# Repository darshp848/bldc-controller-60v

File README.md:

# bldc-controller-60v

A 48 V nominal / 60 V max BLDC motor controller that fits wherever a MAB Robotics MD80 v3.0
fits: same outline, mounting holes, Micro-Fit and AUX connectors, phase-wire holes and
encoder position, with the MD80's 20 A continuous / 80 A peak phase current.

## Status

| Item | State |
|---|---|
| Schematic (KiCad 10, 6 sheets, 137 symbols) | done, ERC 0 errors 0 warnings |
| PCB outline, holes, connectors vs MAB STEP | done, 36 holes match to 0.000 mm (`mech/fit_check.txt`) |
| PCB rev B (144 footprints, 6 layers) | routed; DRC: 0 unconnected, 1 error (MD80-inherent AUX1/screw overlap); two-shunt power stage, 5.0SMDJ60A TVS |
| Simulation | loop inductance, double pulse, bus surge, current loop: docs/simulation.md |
| Firmware | not started; pin map and bring-up values in docs/firmware.md |
| Bench validation | none; loss figures are estimates |

## Layout

```
hardware/            KiCad 10 project (open better-md80.kicad_pro)
  lib/               project symbol (DRV8353S) and MD80 footprints
  better-md80.kicad_dru   60 V clearance rules
docs/
  architecture.md    spec, what limits the MD80 to 48 V, part selection, power tree
  mechanical.md      MD80 fit data and what to verify before first power-up
  thermal_layout.md  loss budget, stack-up, layout rules
  firmware.md        pin map, clocks, DRV8353 settings, protection thresholds
  simulation.md      FastHenry / LTspice / MATLAB results and the changes they call for
  bom.csv            grouped BOM with MPNs
  schematic.pdf      all sheets
mech/                geometry extracted from MAB's MD80_V3.0_simplified.step
sim/                 simulation scripts (outputs in sim/out)
tools/               generators (design.py is the source of truth for the schematic)
```

## Regenerating

```bash
bash tools/build.sh
```

This rebuilds footprints, schematic, netlist, ERC/DRC reports, BOM, the schematic PDF and
the 3D renders. It leaves the routed PCB alone unless you run it with `REGEN_PCB=1`, which
regenerates the placement and throws the routing away (see tools/route.md to redo it).
Schematic changes reach the board through KiCad's Update PCB from Schematic as usual.

`tools/analyze_step.py` needs Python with CadQuery; everything else uses KiCad 10's
`kicad-cli` and bundled Python.

The KiCad files keep their original `better-md80` working name.

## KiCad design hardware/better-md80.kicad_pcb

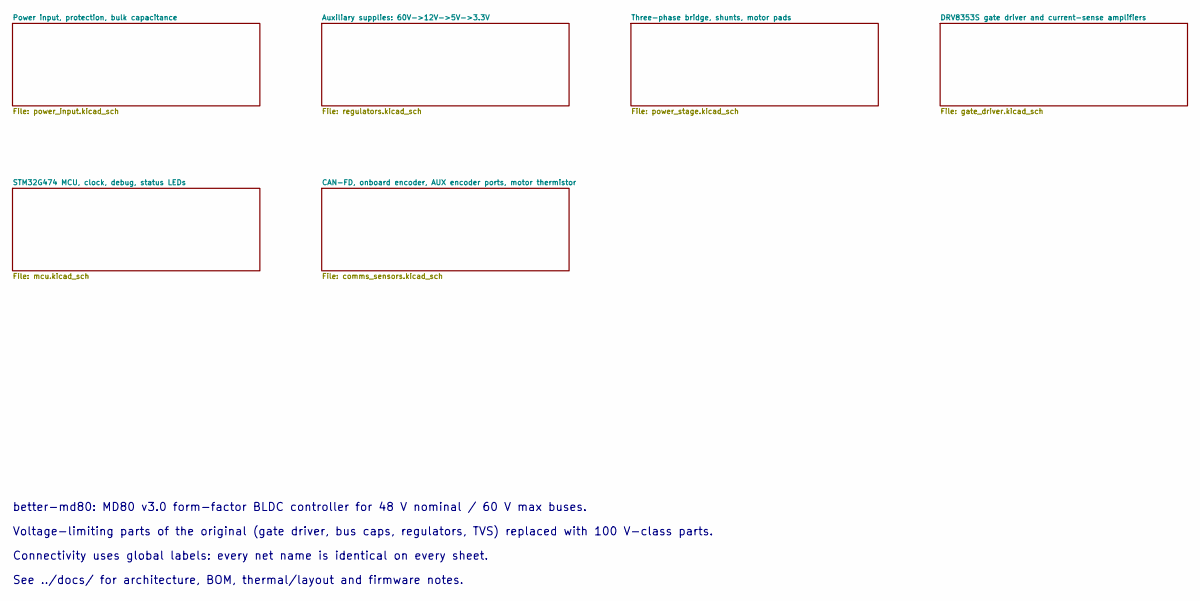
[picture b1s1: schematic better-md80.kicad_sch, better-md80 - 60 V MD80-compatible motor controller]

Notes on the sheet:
better-md80: MD80 v3.0 form-factor BLDC controller for 48 V nominal / 60 V max buses.
Connectivity uses global labels: every net name is identical on every sheet.
Voltage-limiting parts of the original (gate driver, bus caps, regulators, TVS) replaced with 100 V-class parts.
See ../docs/ for architecture, BOM, thermal/layout and firmware notes.

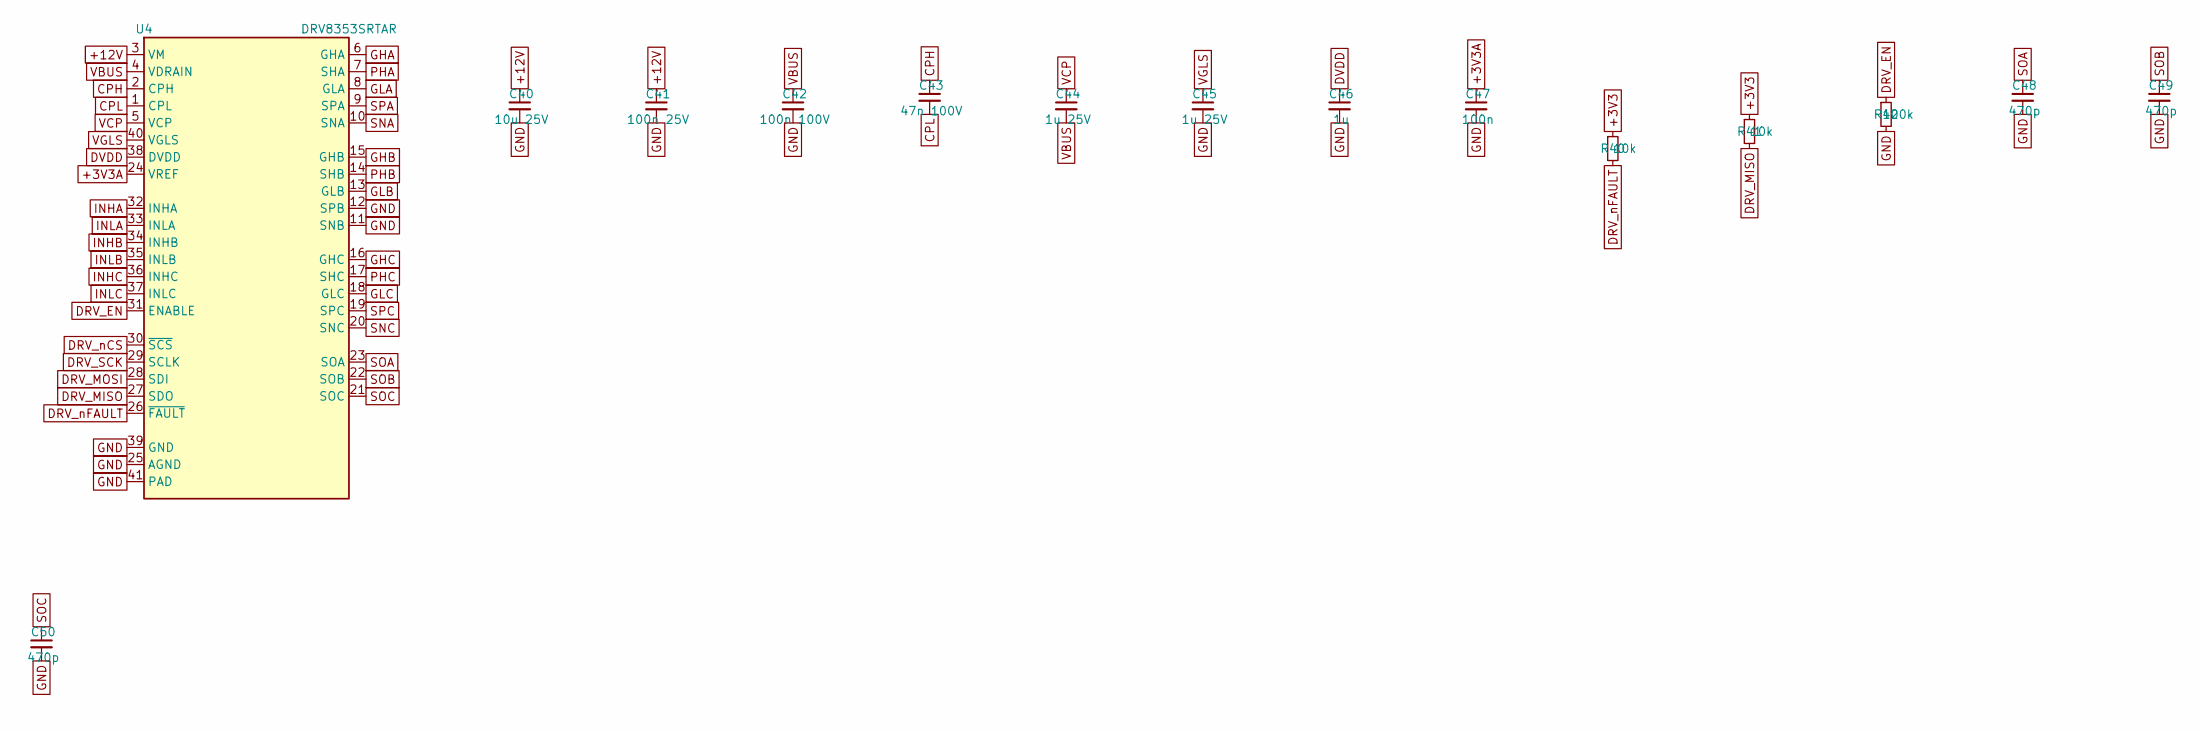
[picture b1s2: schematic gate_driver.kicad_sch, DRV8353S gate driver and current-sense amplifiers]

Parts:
C40: 10u 25V; C_0805_2012Metric
C41: 100n 25V; C_0402_1005Metric
C42: 100n 100V; C_0603_1608Metric; MPN Murata GRM188R72A104KA35D
C43: 47n 100V; C_0603_1608Metric; MPN Murata GRM188R72A473KA01D (verify)
C44, C45: 1u 25V; C_0603_1608Metric
C46: 1u; C_0402_1005Metric
C47: 100n; C_0402_1005Metric
C48, C49, C50: 470p; C_0402_1005Metric
R40, R41: 10k; R_0402_1005Metric
R42: 100k; R_0402_1005Metric
U4: DRV8353SRTAR; Texas_RHA0040B_VQFN-40-1EP_6x6mm_P0.5mm_EP4.15x4.15mm; MPN TI DRV8353SRTAR

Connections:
+3V3: R40.1, R41.1; also elsewhere on the board
+3V3A: C47.1, U4.24 (VREF); also elsewhere on the board
+12V: C40.1, C41.1, U4.3 (VM); also elsewhere on the board
CPH: C43.1, U4.2 (CPH)
CPL: C43.2, U4.1 (CPL)
DRV_EN: R42.1, U4.31 (ENABLE); also elsewhere on the board
DRV_MISO: R41.2, U4.27 (SDO); also elsewhere on the board
DRV_MOSI: U4.28 (SDI); also elsewhere on the board
DRV_SCK: U4.29 (SCLK); also elsewhere on the board
DRV_nCS: U4.30 (~SCS); also elsewhere on the board
DRV_nFAULT: R40.2, U4.26 (~FAULT); also elsewhere on the board
DVDD: C46.1, U4.38 (DVDD)
GHA: U4.6 (GHA); also elsewhere on the board
GHB: U4.15 (GHB); also elsewhere on the board
GHC: U4.16 (GHC); also elsewhere on the board
GLA: U4.8 (GLA); also elsewhere on the board
GLB: U4.13 (GLB); also elsewhere on the board
GLC: U4.18 (GLC); also elsewhere on the board
GND: C40.2, C41.2, C42.2, C45.2, C46.2, C47.2, C48.2, C49.2, C50.2, R42.2, U4.11 (SNB), U4.12 (SPB), U4.25 (AGND), U4.39 (GND), U4.41 (PAD); also elsewhere on the board
INHA: U4.32 (INHA); also elsewhere on the board
INHB: U4.34 (INHB); also elsewhere on the board
INHC: U4.36 (INHC); also elsewhere on the board
INLA: U4.33 (INLA); also elsewhere on the board
INLB: U4.35 (INLB); also elsewhere on the board
INLC: U4.37 (INLC); also elsewhere on the board
PHA: U4.7 (SHA); also elsewhere on the board
PHB: U4.14 (SHB); also elsewhere on the board
PHC: U4.17 (SHC); also elsewhere on the board
SNA: U4.10 (SNA); also elsewhere on the board
SNC: U4.20 (SNC); also elsewhere on the board
SOA: C48.1, U4.23 (SOA); also elsewhere on the board
SOB: C49.1, U4.22 (SOB); also elsewhere on the board
SOC: C50.1, U4.21 (SOC); also elsewhere on the board
SPA: U4.9 (SPA); also elsewhere on the board
SPC: U4.19 (SPC); also elsewhere on the board
VBUS: C42.1, C44.2, U4.4 (VDRAIN); also elsewhere on the board
VCP: C44.1, U4.5 (VCP)
VGLS: C45.1, U4.40 (VGLS)

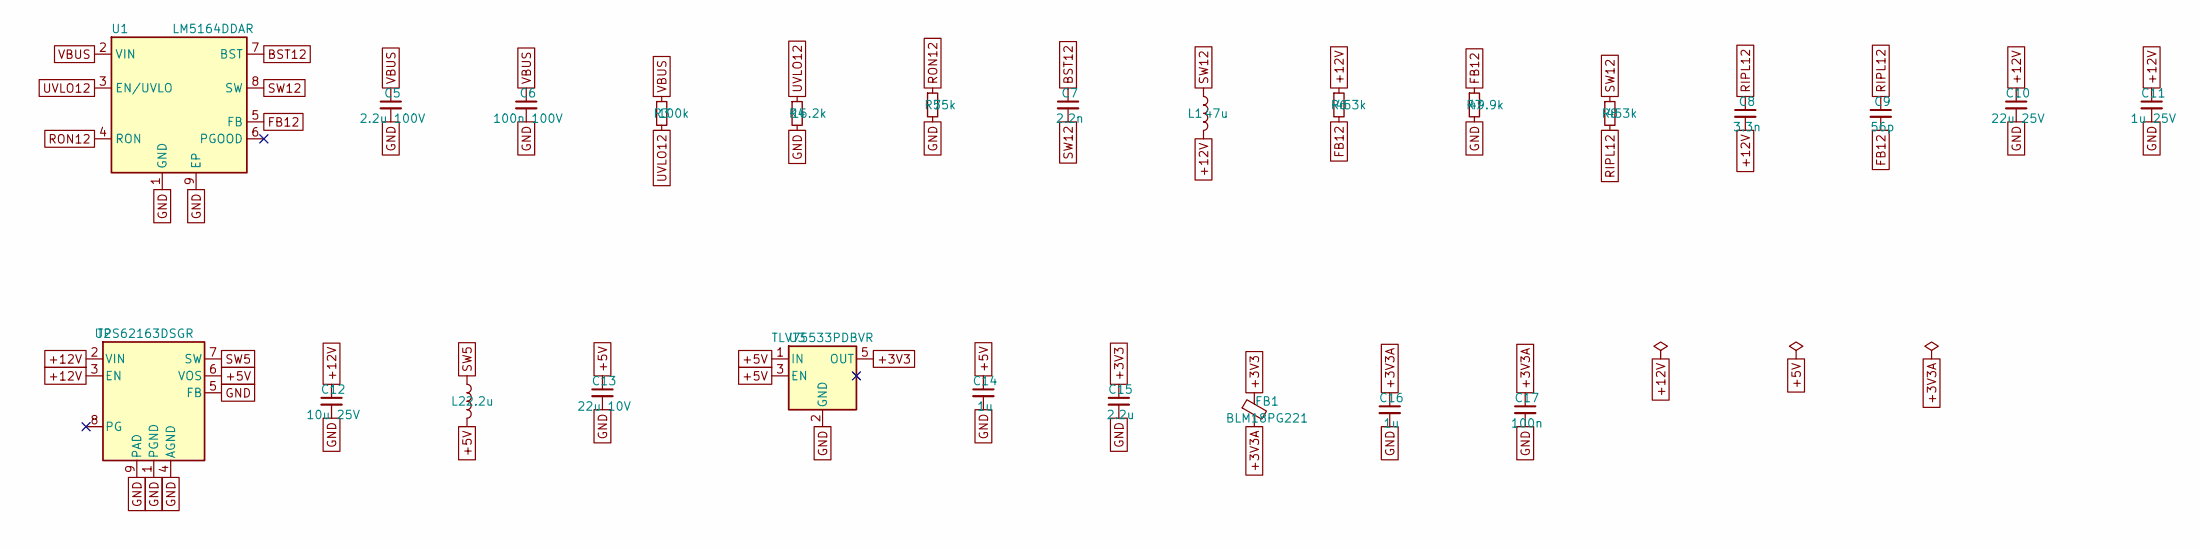
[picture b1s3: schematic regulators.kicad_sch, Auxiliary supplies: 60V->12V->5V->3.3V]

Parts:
C5: 2.2u 100V; C_1206_3216Metric; MPN TDK C3216X7S2A225K160AB
C6: 100n 100V; C_0603_1608Metric; MPN Murata GRM188R72A104KA35D
C7: 2.2n; C_0402_1005Metric
C8: 3.3n; C_0402_1005Metric
C9: 56p; C_0402_1005Metric
C10: 22u 25V; C_1210_3225Metric; MPN Taiyo Yuden TMK325B7226KMHT
C11: 1u 25V; C_0603_1608Metric
C12: 10u 25V; C_0805_2012Metric
C13: 22u 10V; C_0805_2012Metric
C14, C16: 1u; C_0402_1005Metric
C15: 2.2u; C_0603_1608Metric
C17: 100n; C_0402_1005Metric
FB1: BLM18PG221; L_0603_1608Metric; MPN Murata BLM18PG221SN1D
L1: 47u; L_Bourns-SRN4018; MPN Bourns SRN4018-470M (verify Isat)
L2: 2.2u; L_1008_2520Metric; MPN Murata DFE252012F-2R2M
R3: 100k; R_0603_1608Metric
R4: 16.2k; R_0402_1005Metric
R5: 75k; R_0402_1005Metric
R6: 453k; R_0402_1005Metric
R7: 49.9k; R_0402_1005Metric
R8: 453k; R_0603_1608Metric
U1: LM5164DDAR; Texas_HSOP-8-1EP_3.9x4.9mm_P1.27mm; MPN TI LM5164DDAR
U2: TPS62163DSGR; Texas_DSG0008A_WSON-8-1EP_2x2mm_P0.5mm_EP0.9x1.6mm; MPN TI TPS62163DSGR
U3: TLV75533PDBVR; SOT-23-5; MPN TI TLV75533PDBVR

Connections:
+3V3: C15.1, FB1.1, U3.5 (OUT); also elsewhere on the board
+3V3A: C16.1, C17.1, FB1.2; also elsewhere on the board
+5V: C13.1, C14.1, L2.2, U2.6 (VOS), U3.1 (IN), U3.3 (EN); also elsewhere on the board
+12V: C8.2, C10.1, C11.1, C12.1, L1.2, R6.1, U2.2 (VIN), U2.3 (EN); also elsewhere on the board
BST12: C7.1, U1.7 (BST)
FB12: C9.2, R6.2, R7.1, U1.5 (FB)
GND: C5.2, C6.2, C10.2, C11.2, C12.2, C13.2, C14.2, C15.2, C16.2, C17.2, R4.2, R5.2, R7.2, U1.1 (GND), U1.9 (EP), U2.1 (PGND), U2.4 (AGND), U2.5 (FB), U2.9 (PAD), U3.2 (GND); also elsewhere on the board
RIPL12: C8.1, C9.1, R8.2
RON12: R5.1, U1.4 (RON)
SW5: L2.1, U2.7 (SW)
SW12: C7.2, L1.1, R8.1, U1.8 (SW)
UVLO12: R3.2, R4.1, U1.3 (EN/UVLO)
VBUS: C5.1, C6.1, R3.1, U1.2 (VIN); also elsewhere on the board

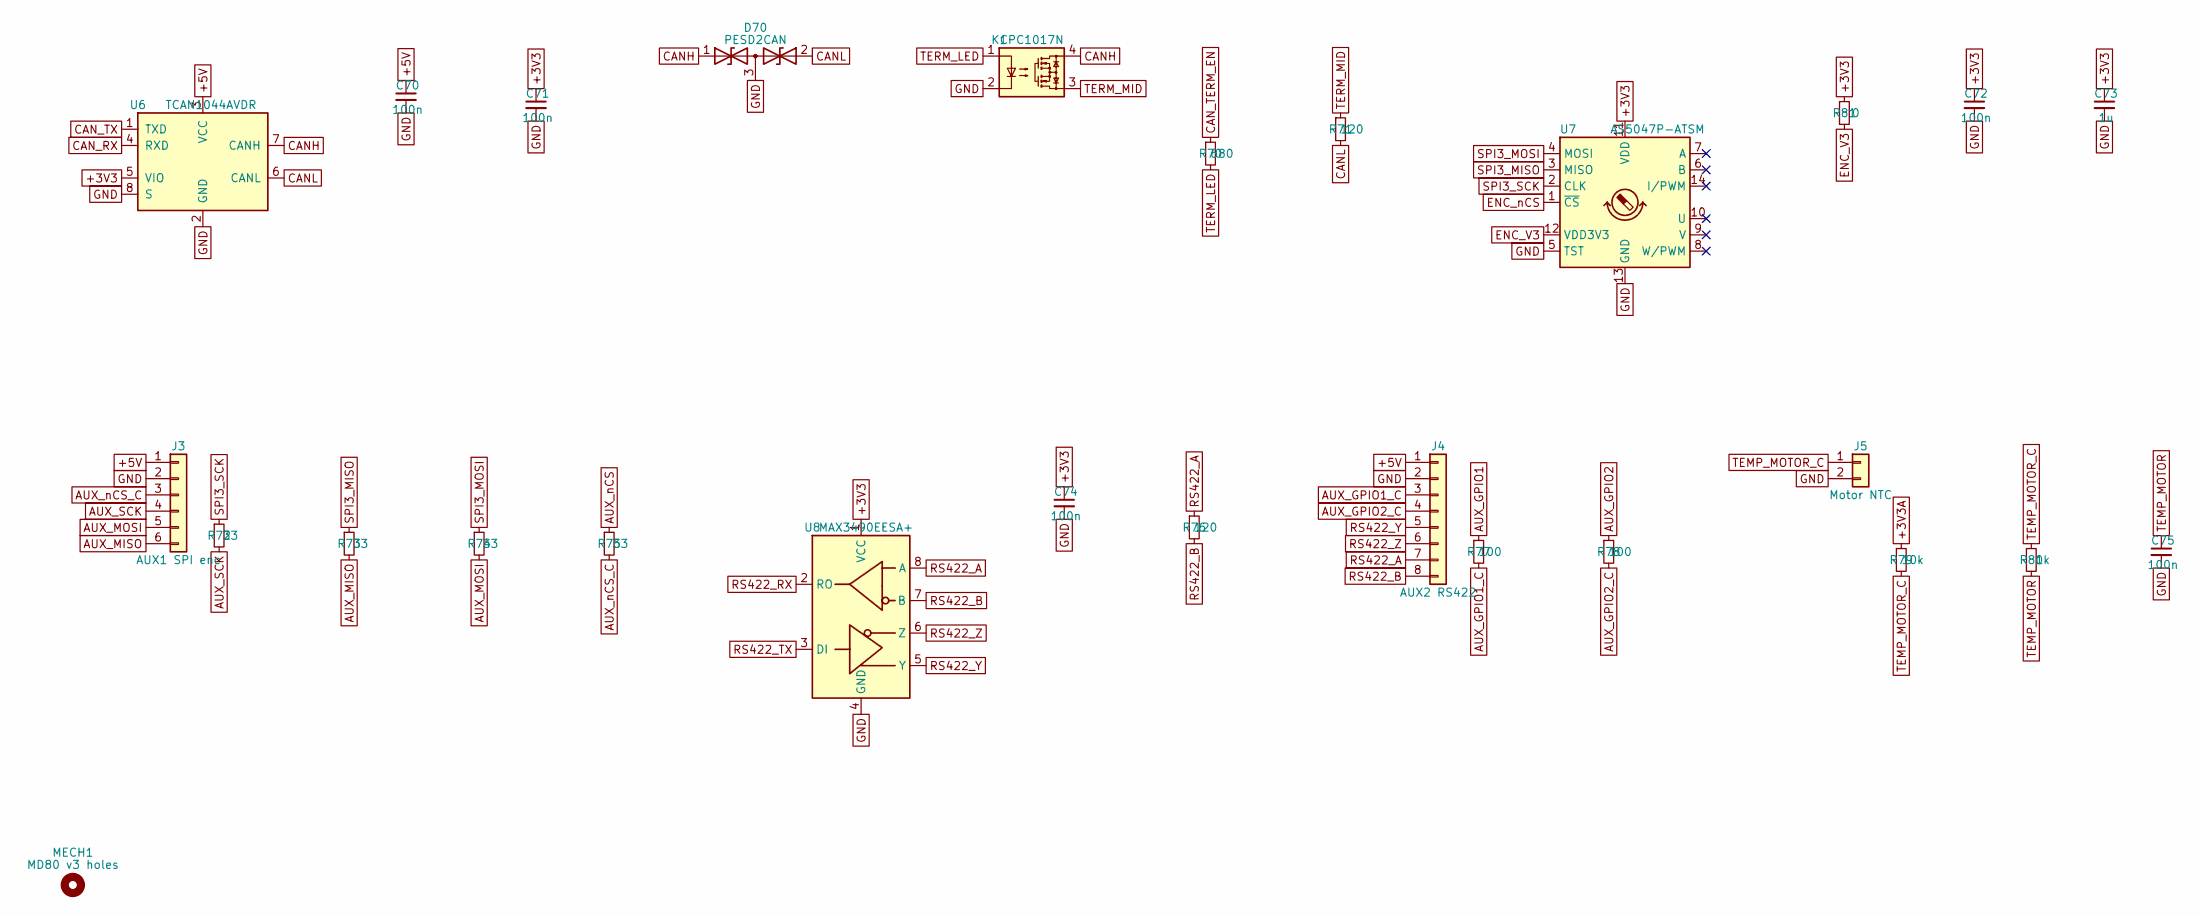
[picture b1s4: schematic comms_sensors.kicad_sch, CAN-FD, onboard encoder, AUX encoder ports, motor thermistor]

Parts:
C70, C71, C72, C74, C75: 100n; C_0402_1005Metric
C73: 1u; C_0402_1005Metric
D70: PESD2CAN; SOT-23; MPN Nexperia PESD2CAN,215
J3: AUX1 SPI enc; Molex_PicoBlade_53048-0610_1x06_P1.25mm_Horizontal; MPN Molex 53048-0650
J4: AUX2 RS422; Molex_PicoBlade_53048-0810_1x08_P1.25mm_Horizontal; MPN Molex 53048-0850
J5: Motor NTC; MD80_NTC_Pads
K1: CPC1017N; SOP-4_3.8x4.1mm_P2.54mm; MPN IXYS CPC1017NTR
MECH1: MD80 v3 holes; MD80_V3_Mechanical
R70: 680; R_0402_1005Metric
R71, R76: 120; R_0603_1608Metric
R72, R73, R74, R75: 33; R_0402_1005Metric
R77, R78: 100; R_0402_1005Metric
R79: 10k; R_0402_1005Metric
R80: 1k; R_0402_1005Metric
R81: 0; R_0402_1005Metric
U6: TCAN1044AVDR; SOIC-8_3.9x4.9mm_P1.27mm; MPN TI TCAN1044AVDR
U7: AS5047P-ATSM; TSSOP-14_4.4x5mm_P0.65mm; MPN ams OSRAM AS5047P-ATSM
U8: MAX3490EESA+; SOIC-8_3.9x4.9mm_P1.27mm; MPN Analog MAX3490EESA+

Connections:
+3V3: C71.1, C72.1, C73.1, C74.1, R81.1, U6.5 (VIO), U7.11 (VDD), U8.1 (VCC); also elsewhere on the board
+3V3A: R79.1; also elsewhere on the board
+5V: C70.1, J3.1, J4.1, U6.3 (VCC); also elsewhere on the board
AUX_GPIO1: R77.1; also elsewhere on the board
AUX_GPIO1_C: J4.3, R77.2
AUX_GPIO2: R78.1; also elsewhere on the board
AUX_GPIO2_C: J4.4, R78.2
AUX_MISO: J3.6, R73.2
AUX_MOSI: J3.5, R74.2
AUX_SCK: J3.4, R72.2
AUX_nCS: R75.1; also elsewhere on the board
AUX_nCS_C: J3.3, R75.2
CANH: D70.1 (A1), K1.4, U6.7 (CANH); also elsewhere on the board
CANL: D70.2 (A2), R71.2, U6.6 (CANL); also elsewhere on the board
CAN_RX: U6.4 (RXD); also elsewhere on the board
CAN_TERM_EN: R70.1; also elsewhere on the board
CAN_TX: U6.1 (TXD); also elsewhere on the board
ENC_V3: R81.2, U7.12 (VDD3V3)
ENC_nCS: U7.1 (~CS); also elsewhere on the board
GND: C70.2, C71.2, C72.2, C73.2, C74.2, C75.2, D70.3 (common), J3.2, J4.2, J5.2, K1.2, U6.2 (GND), U6.8 (S), U7.5 (TST), U7.13 (GND), U8.4 (GND); also elsewhere on the board
RS422_A: J4.7, R76.1, U8.8 (A)
RS422_B: J4.8, R76.2, U8.7 (B)
RS422_RX: U8.2 (RO); also elsewhere on the board
RS422_TX: U8.3 (DI); also elsewhere on the board
RS422_Y: J4.5, U8.5 (Y)
RS422_Z: J4.6, U8.6 (Z)
SPI3_MISO: R73.1, U7.3 (MISO); also elsewhere on the board
SPI3_MOSI: R74.1, U7.4 (MOSI); also elsewhere on the board
SPI3_SCK: R72.1, U7.2 (CLK); also elsewhere on the board
TEMP_MOTOR: C75.1, R80.2; also elsewhere on the board
TEMP_MOTOR_C: J5.1, R79.2, R80.1
TERM_LED: K1.1, R70.2
TERM_MID: K1.3, R71.1

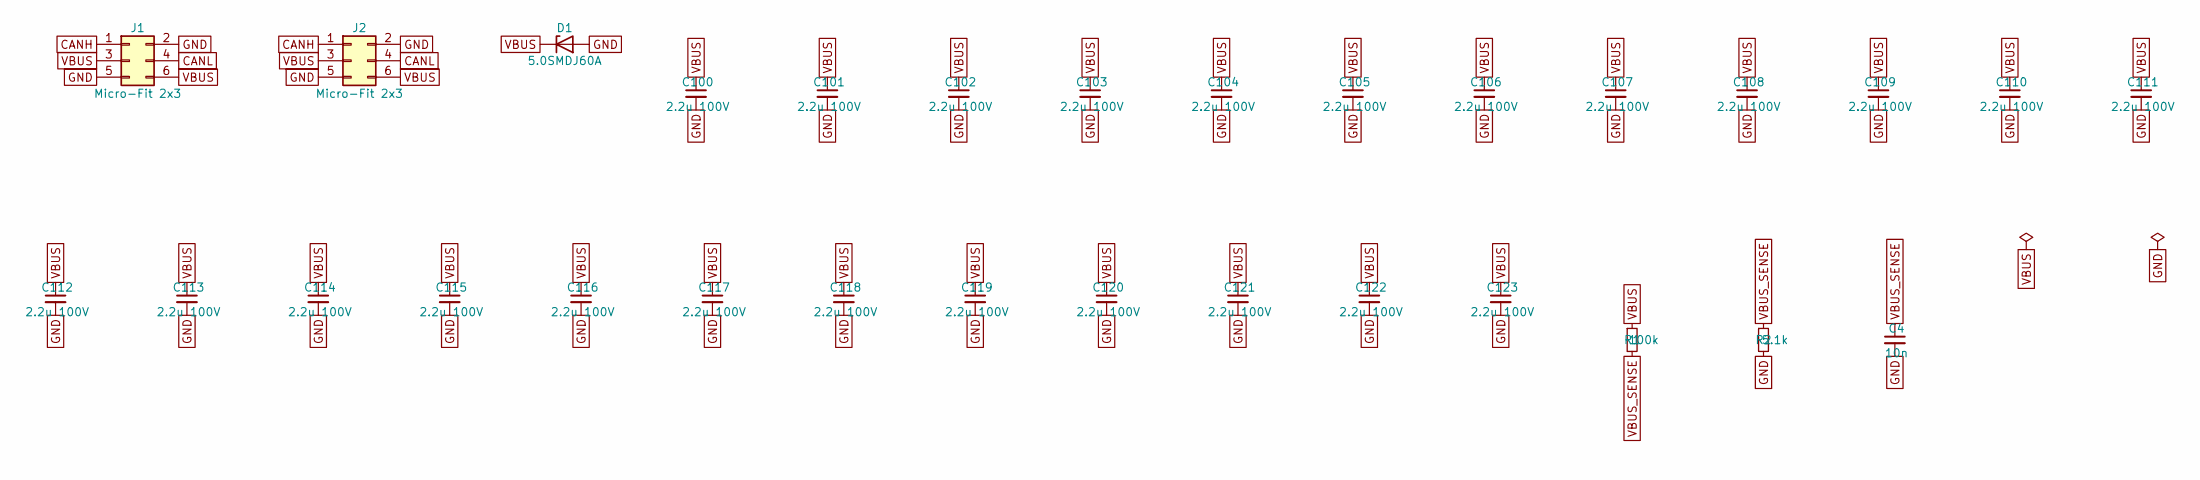
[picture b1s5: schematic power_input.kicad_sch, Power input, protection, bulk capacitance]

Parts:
C4: 10n; C_0402_1005Metric
C100, C101, C102, C103, C104, C105, C106, C107, C108, C109, C110, C111, C112, C113, C114, C115, C116, C117, C118, C119, C120, C121, C122, C123: 2.2u 100V; C_1206_3216Metric; MPN TDK C3216X7S2A225K160AB
D1: 5.0SMDJ60A; D_SMC; MPN Littelfuse 5.0SMDJ60A
J1, J2: Micro-Fit 2x3; MD80_MicroFit_2x03_RA; MPN Molex 43045-0600 (R/A, 2x3)
R1: 100k; R_0603_1608Metric
R2: 5.1k; R_0402_1005Metric

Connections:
CANH: J1.1, J2.1; also elsewhere on the board
CANL: J1.4, J2.4; also elsewhere on the board
GND: C4.2, C100.2, C101.2, C102.2, C103.2, C104.2, C105.2, C106.2, C107.2, C108.2, C109.2, C110.2, C111.2, C112.2, C113.2, C114.2, C115.2, C116.2, C117.2, C118.2, C119.2, C120.2, C121.2, C122.2, C123.2, D1.2 (A), J1.2, J1.5, J2.2, J2.5, R2.2; also elsewhere on the board
VBUS: C100.1, C101.1, C102.1, C103.1, C104.1, C105.1, C106.1, C107.1, C108.1, C109.1, C110.1, C111.1, C112.1, C113.1, C114.1, C115.1, C116.1, C117.1, C118.1, C119.1, C120.1, C121.1, C122.1, C123.1, D1.1 (K), J1.3, J1.6, J2.3, J2.6, R1.1; also elsewhere on the board
VBUS_SENSE: C4.1, R1.2, R2.1; also elsewhere on the board

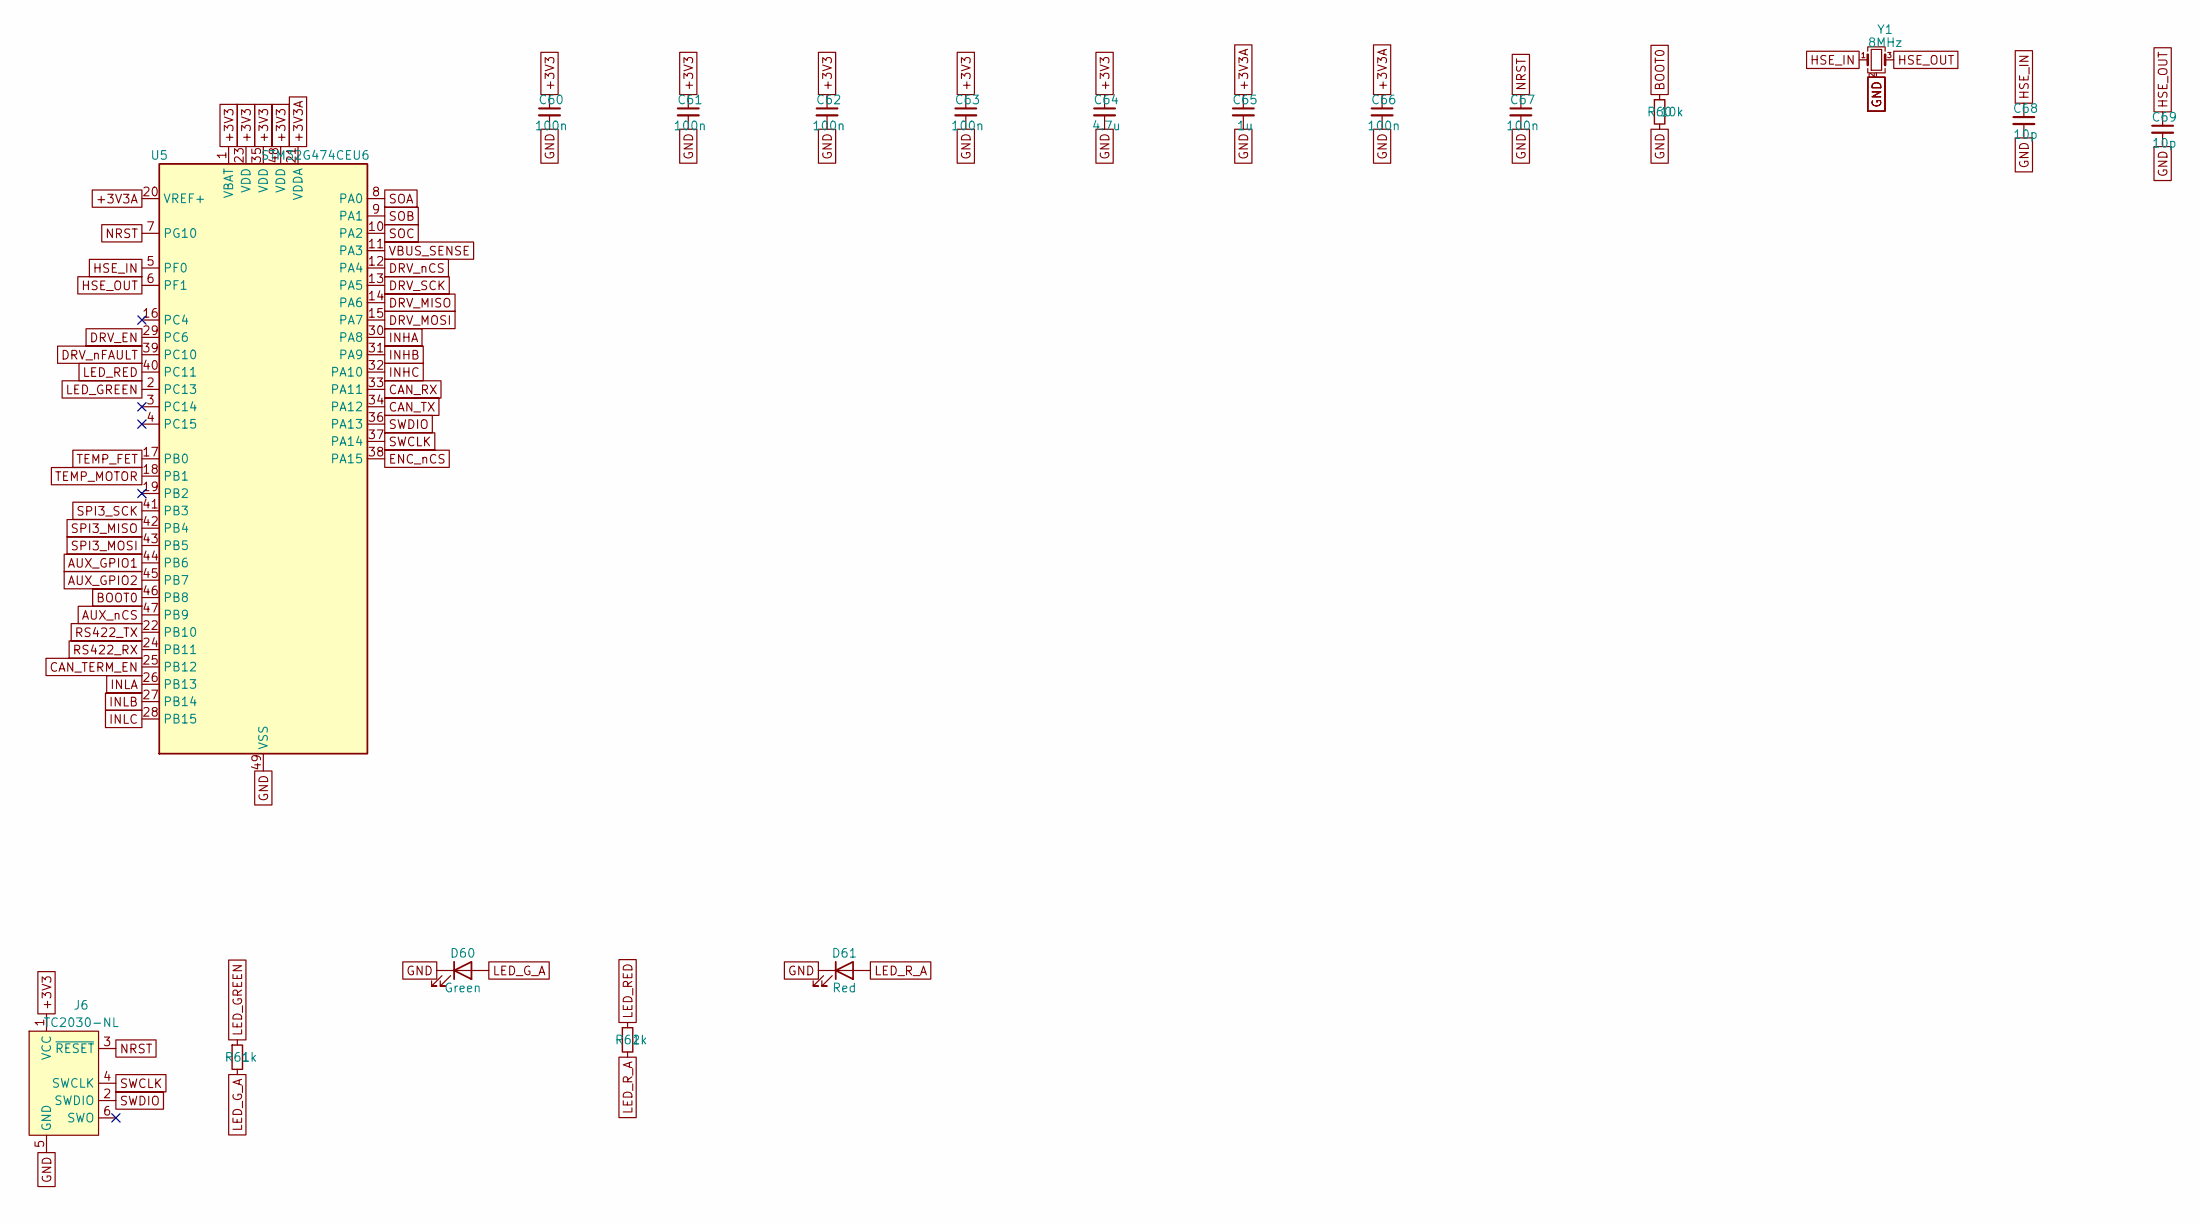
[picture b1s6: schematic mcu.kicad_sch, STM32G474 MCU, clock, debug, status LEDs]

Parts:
C60, C61, C62, C63, C66, C67: 100n; C_0402_1005Metric
C64: 4.7u; C_0603_1608Metric
C65: 1u; C_0402_1005Metric
C68, C69: 10p; C_0402_1005Metric
D60: Green; LED_0603_1608Metric; MPN Kingbright APTD1608LZGCK
D61: Red; LED_0603_1608Metric; MPN Kingbright APTD1608LSURCK
J6: TC2030-NL; Tag-Connect_TC2030-IDC-NL_2x03_P1.27mm_Vertical
R60: 10k; R_0402_1005Metric
R61, R62: 1k; R_0402_1005Metric
U5: STM32G474CEU6; QFN-48-1EP_7x7mm_P0.5mm_EP5.6x5.6mm; MPN ST STM32G474CEU6
Y1: 8MHz; Crystal_SMD_3225-4Pin_3.2x2.5mm; MPN Abracon ABM8-8.000MHZ-B2-T (verify CL)

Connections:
+3V3: C60.1, C61.1, C62.1, C63.1, C64.1, J6.1 (VCC), U5.1 (VBAT), U5.23 (VDD), U5.35 (VDD), U5.48 (VDD); also elsewhere on the board
+3V3A: C65.1, C66.1, U5.20 (VREF+), U5.21 (VDDA); also elsewhere on the board
AUX_GPIO1: U5.44 (PB6); also elsewhere on the board
AUX_GPIO2: U5.45 (PB7); also elsewhere on the board
AUX_nCS: U5.47 (PB9); also elsewhere on the board
BOOT0: R60.1, U5.46 (PB8)
CAN_RX: U5.33 (PA11); also elsewhere on the board
CAN_TERM_EN: U5.25 (PB12); also elsewhere on the board
CAN_TX: U5.34 (PA12); also elsewhere on the board
DRV_EN: U5.29 (PC6); also elsewhere on the board
DRV_MISO: U5.14 (PA6); also elsewhere on the board
DRV_MOSI: U5.15 (PA7); also elsewhere on the board
DRV_SCK: U5.13 (PA5); also elsewhere on the board
DRV_nCS: U5.12 (PA4); also elsewhere on the board
DRV_nFAULT: U5.39 (PC10); also elsewhere on the board
ENC_nCS: U5.38 (PA15); also elsewhere on the board
GND: C60.2, C61.2, C62.2, C63.2, C64.2, C65.2, C66.2, C67.2, C68.2, C69.2, D60.1 (K), D61.1 (K), J6.5 (GND), R60.2, U5.49 (VSS), Y1.2 (G), Y1.4 (G); also elsewhere on the board
HSE_IN: C68.1, U5.5 (PF0), Y1.1
HSE_OUT: C69.1, U5.6 (PF1), Y1.3
INHA: U5.30 (PA8); also elsewhere on the board
INHB: U5.31 (PA9); also elsewhere on the board
INHC: U5.32 (PA10); also elsewhere on the board
INLA: U5.26 (PB13); also elsewhere on the board
INLB: U5.27 (PB14); also elsewhere on the board
INLC: U5.28 (PB15); also elsewhere on the board
LED_GREEN: R61.1, U5.2 (PC13)
LED_G_A: D60.2 (A), R61.2
LED_RED: R62.1, U5.40 (PC11)
LED_R_A: D61.2 (A), R62.2
NRST: C67.1, J6.3 (~RESET), U5.7 (PG10)
RS422_RX: U5.24 (PB11); also elsewhere on the board
RS422_TX: U5.22 (PB10); also elsewhere on the board
SOA: U5.8 (PA0); also elsewhere on the board
SOB: U5.9 (PA1); also elsewhere on the board
SOC: U5.10 (PA2); also elsewhere on the board
SPI3_MISO: U5.42 (PB4); also elsewhere on the board
SPI3_MOSI: U5.43 (PB5); also elsewhere on the board
SPI3_SCK: U5.41 (PB3); also elsewhere on the board
SWCLK: J6.4 (SWCLK), U5.37 (PA14)
SWDIO: J6.2 (SWDIO), U5.36 (PA13)
TEMP_FET: U5.17 (PB0); also elsewhere on the board
TEMP_MOTOR: U5.18 (PB1); also elsewhere on the board
VBUS_SENSE: U5.11 (PA3); also elsewhere on the board

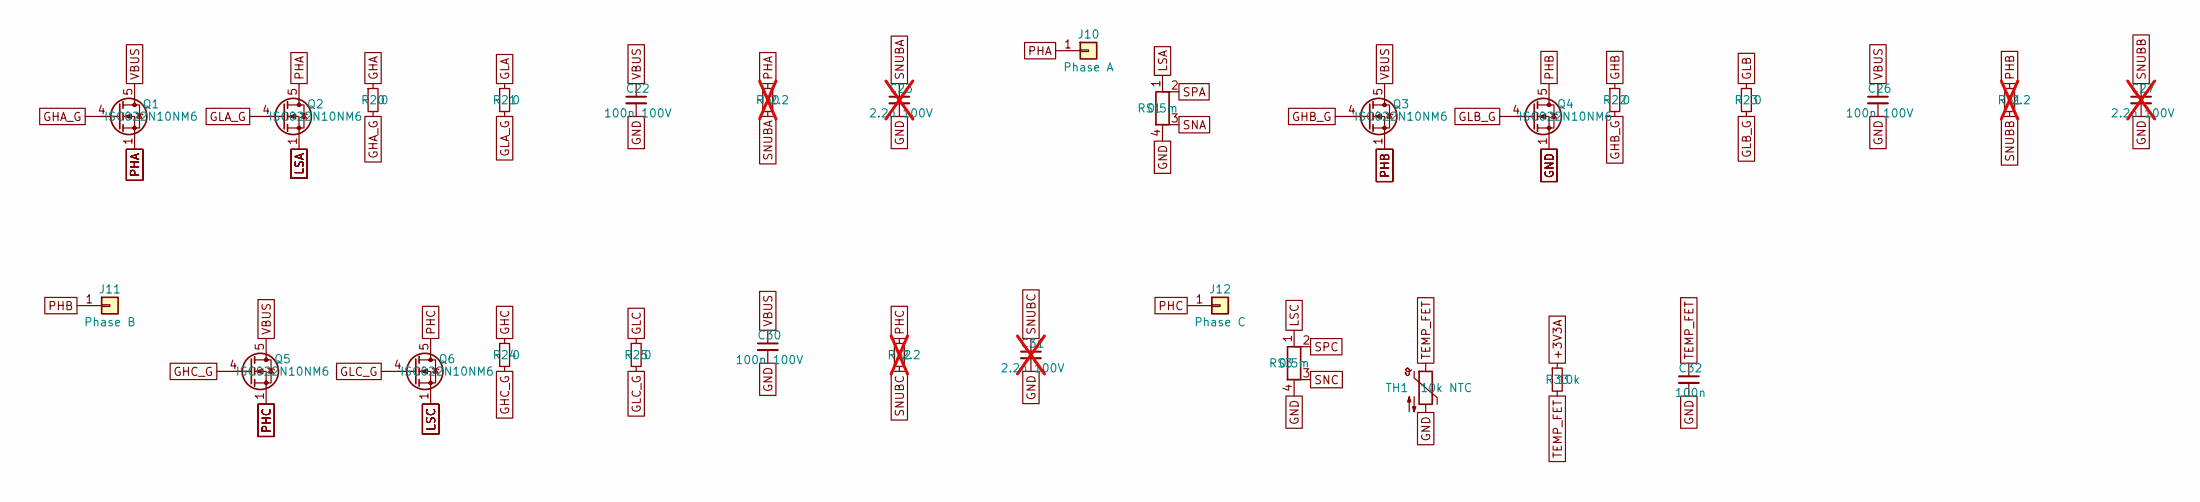
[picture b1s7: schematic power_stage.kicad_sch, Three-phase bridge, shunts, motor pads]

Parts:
C22, C26, C30: 100n 100V; C_0603_1608Metric; MPN Murata GRM188R72A104KA35D
C23, C27, C31: 2.2n 100V; C_0603_1608Metric; not fitted
C32: 100n; C_0402_1005Metric
J10: Phase A; MD80_Phase_Pad
J11: Phase B; MD80_Phase_Pad
J12: Phase C; MD80_Phase_Pad
Q1, Q2, Q3, Q4, Q5, Q6: ISC022N10NM6; TDSON-8-1; MPN Infineon ISC022N10NM6ATMA1
R20, R21, R22, R23, R24, R25: 0; R_0402_1005Metric
R30, R31, R32: 2.2; R_1206_3216Metric; not fitted
R33: 10k; R_0402_1005Metric
RS1, RS3: 0.5m; R_Shunt_Vishay_WSK2512_6332Metric_T2.66mm; MPN Vishay WSK2512 0.5 mOhm 1% (verify)
TH1: 10k NTC; R_0603_1608Metric; MPN Murata NCP18XH103F03RB

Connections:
+3V3A: R33.1; also elsewhere on the board
GHA: R20.1; also elsewhere on the board
GHA_G: Q1.4 (G), R20.2
GHB: R22.1; also elsewhere on the board
GHB_G: Q3.4 (G), R22.2
GHC: R24.1; also elsewhere on the board
GHC_G: Q5.4 (G), R24.2
GLA: R21.1; also elsewhere on the board
GLA_G: Q2.4 (G), R21.2
GLB: R23.1; also elsewhere on the board
GLB_G: Q4.4 (G), R23.2
GLC: R25.1; also elsewhere on the board
GLC_G: Q6.4 (G), R25.2
GND: C22.2, C23.2, C26.2, C27.2, C30.2, C31.2, C32.2, Q4.1 (S), Q4.2 (S), Q4.3 (S), RS1.4, RS3.4, TH1.2; also elsewhere on the board
LSA: Q2.1 (S), Q2.2 (S), Q2.3 (S), RS1.1
LSC: Q6.1 (S), Q6.2 (S), Q6.3 (S), RS3.1
PHA: J10.1, Q1.1 (S), Q1.2 (S), Q1.3 (S), Q2.5 (D), R30.1; also elsewhere on the board
PHB: J11.1, Q3.1 (S), Q3.2 (S), Q3.3 (S), Q4.5 (D), R31.1; also elsewhere on the board
PHC: J12.1, Q5.1 (S), Q5.2 (S), Q5.3 (S), Q6.5 (D), R32.1; also elsewhere on the board
SNA: RS1.3; also elsewhere on the board
SNC: RS3.3; also elsewhere on the board
SNUBA: C23.1, R30.2
SNUBB: C27.1, R31.2
SNUBC: C31.1, R32.2
SPA: RS1.2; also elsewhere on the board
SPC: RS3.2; also elsewhere on the board
TEMP_FET: C32.1, R33.2, TH1.1; also elsewhere on the board
VBUS: C22.1, C26.1, C30.1, Q1.5 (D), Q3.5 (D), Q5.5 (D); also elsewhere on the board
